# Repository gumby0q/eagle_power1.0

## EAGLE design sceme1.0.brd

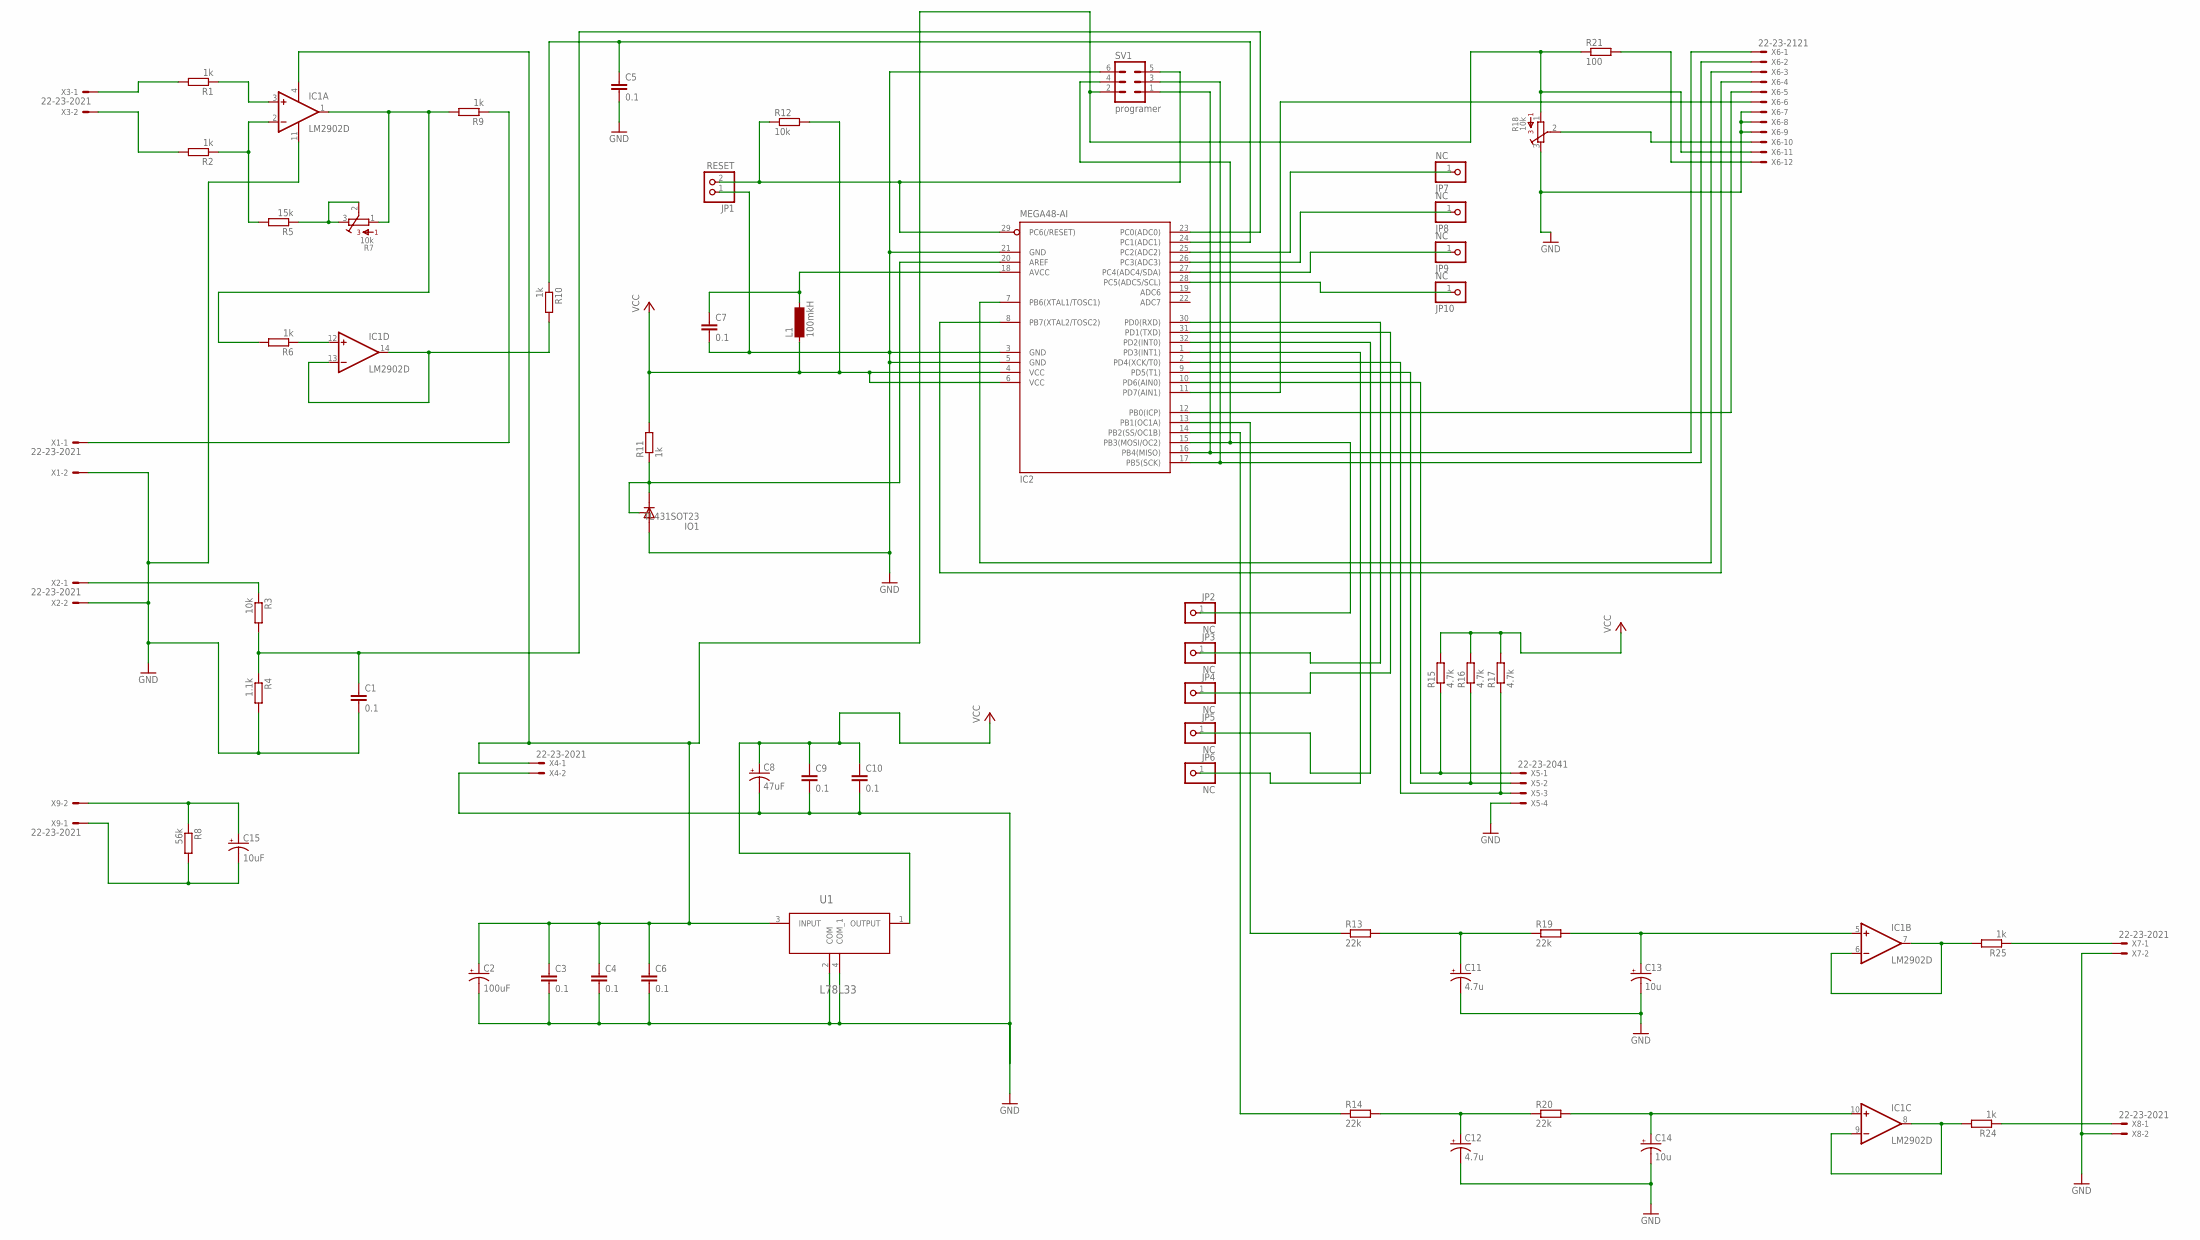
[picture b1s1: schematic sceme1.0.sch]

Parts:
C1, C3, C4, C5, C6, C7, C9, C10: 0.1; C0805
C2: 100uF; E2,5-5
C8: 47uF; E2,5-5
C11, C12: 4.7u; E2,5-5
C13, C14: 10u; E2,5-5
C15: 10uF; E2,5-5
IC1: LM2902D; SO14
IC2: MEGA48-AI; TQFP32-08
IO1: TL431SOT23; SOT23
JP1: RESET; 1X02
JP2, JP3, JP4, JP5, JP6, JP7, JP8, JP9, JP10: NC; 1X01
L1: 100mkH; SM-1206
R1, R2, R6, R9, R10, R11, R24, R25: 1k; R0805
R3, R12: 10k; R0805
R4: 1.1k; R0805
R5: 15k; R0805
R7, R18: 10k; 3362P
R8: 56k; R0805
R13, R14, R19, R20: 22k; R0805
R15, R16, R17: 4.7k; R0805
R21: 100; R0805
SV1: programer; ML6
U1: L78L33; SOT150P400X160-4N
X1, X2, X3, X4, X7, X8, X9: 22-23-2021
X5: 22-23-2041
X6: 22-23-2121

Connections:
GND: C1.2, C2.-, C3.2, C4.2, C5.2, C6.2, C7.2, C8.-, C9.2, C10.2, C11.-, C12.-, C13.-, C14.-, IC1.11 (V-), IC2.3 (GND), IC2.5 (GND), IC2.21 (GND), IO1.3 (A), JP1.1, R4.2, R18.3, SV1.6, U1.2 (COM), U1.4 (COM_1), X1.2, X2.2, X4.2, X5.4, X6.7, X6.8, X6.9, X7.2, X8.2
unnamed: C11.+, R13.2, R19.1
unnamed: C13.+, IC1.5 (+IN), R19.2
unnamed: C12.+, R14.2, R20.1
unnamed: C14.+, IC1.10 (+IN), R20.2
unnamed: IC2.20 (AREF), IO1.1 (C), IO1.2 (R), R11.1
unnamed: IC2.12 (PB0(ICP)), X6.5
unnamed: IC2.11 (PD7(AIN1)), X6.6
unnamed: R21.2, X6.12
unnamed: C15.+, R8.1, X9.2
unnamed: C7.1, IC2.18 (AVCC), L1.2
unnamed: R18.2, X6.10
unnamed: IC2.29 (PC6(/RESET)), JP1.2, R12.1, SV1.5
unnamed: C15.-, R8.2, X9.1
unnamed: IC2.7 (PB6(XTAL1/TOSC1)), X6.3
unnamed: IC2.17 (PB5(SCK)), SV1.3, X6.2
unnamed: IC2.16 (PB4(MISO)), SV1.1, X6.1
unnamed: IC2.30 (PD0(RXD)), JP3.1
unnamed: IC2.31 (PD1(TXD)), JP4.1
unnamed: IC2.10 (PD6(AIN0)), R15.1, X5.1
unnamed: IC2.9 (PD5(T1)), R16.1, X5.2
unnamed: IC2.2 (PD4(XCK/T0)), R17.1, X5.3
unnamed: IC2.32 (PD2(INT0)), JP5.1
unnamed: IC2.1 (PD3(INT1)), JP6.1
unnamed: IC2.8 (PB7(XTAL2/TOSC2)), X6.4
unnamed: IC2.13 (PB1(OC1A)), R13.1
unnamed: IC2.14 (PB2(SS/OC1B)), R14.1
unnamed: IC2.15 (PB3(MOSI/OC2)), JP2.1, SV1.4
unnamed: IC1.8 (OUT), IC1.9 (-IN), R24.2
unnamed: IC1.6 (-IN), IC1.7 (OUT), R25.2
unnamed: IC1.3 (+IN), R1.1
unnamed: IC1.2 (-IN), R2.1, R5.2
unnamed: R5.1, R7.2, R7.3
unnamed: IC1.1 (OUT), R6.2, R7.1, R9.2
unnamed: R1.2, X3.1
unnamed: R25.1, X7.1
unnamed: IC1.12 (+IN), R6.1
unnamed: C5.1, IC2.24 (PC1(ADC1)), R10.1
unnamed: R24.1, X8.1
unnamed: R9.1, X1.1
unnamed: R2.2, X3.2
unnamed: C1.1, IC2.23 (PC0(ADC0)), R3.2, R4.1
unnamed: R3.1, X2.1
unnamed: IC2.25 (PC2(ADC2)), JP7.1
unnamed: IC2.26 (PC3(ADC3)), JP8.1
unnamed: IC1.13 (-IN), IC1.14 (OUT), R10.2
unnamed: IC2.27 (PC4(ADC4/SDA)), JP9.1
unnamed: IC2.28 (PC5(ADC5/SCL)), JP10.1
unnamed: C2.+, C3.1, C4.1, C6.1, IC1.4 (V+), R18.1, R21.1, SV1.2, U1.3 (INPUT), X4.1, X6.11
VCC: C8.+, C9.1, C10.1, IC2.4 (VCC), IC2.6 (VCC), L1.1, R11.2, R12.2, R15.2, R16.2, R17.2, U1.1 (OUTPUT)

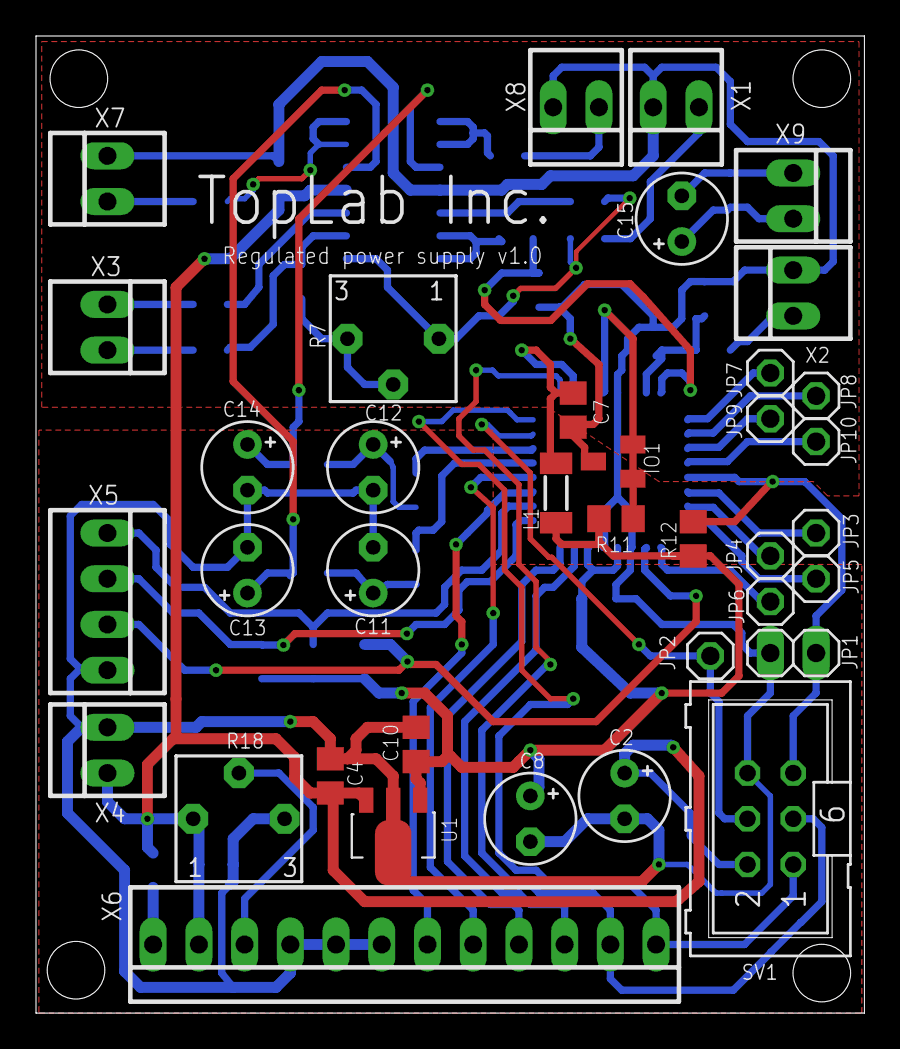
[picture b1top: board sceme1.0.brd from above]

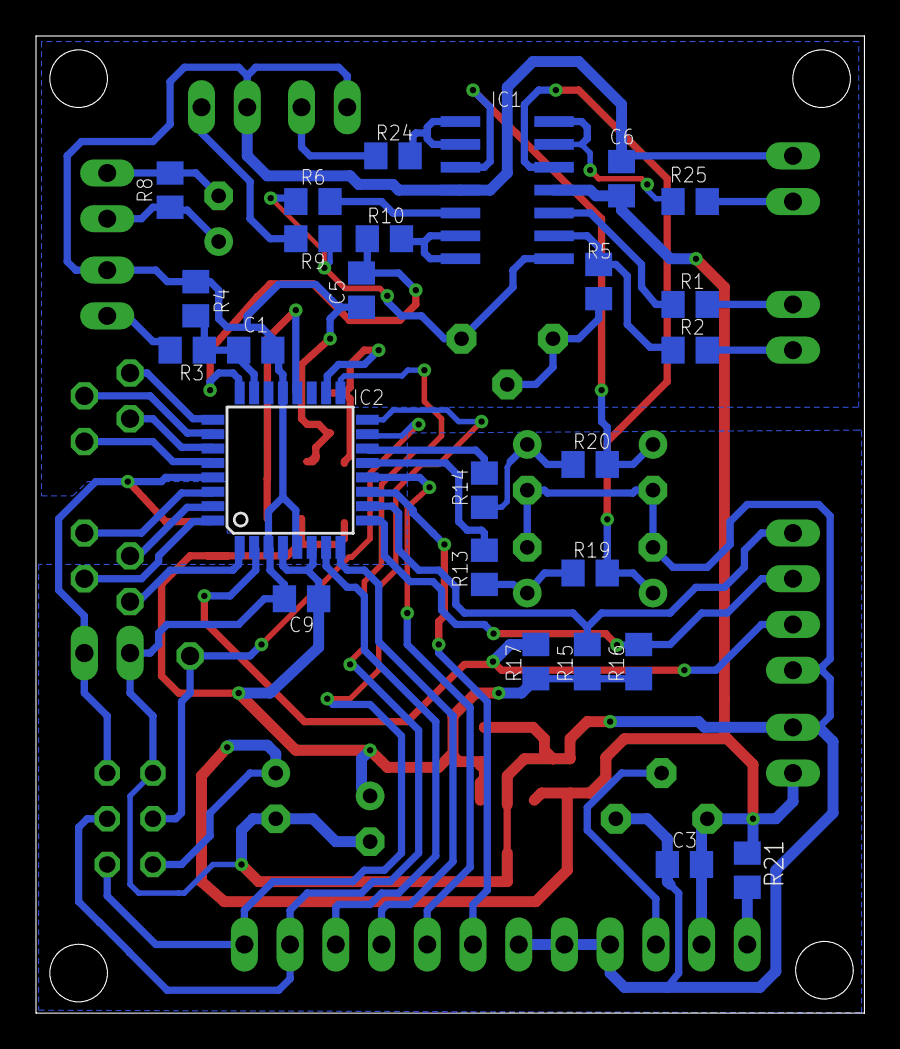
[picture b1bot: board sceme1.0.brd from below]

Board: 2 copper layers, 46.0 x 54.3 mm, 63 parts (26 on the bottom side), 50 nets.
